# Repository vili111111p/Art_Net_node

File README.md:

# Art_Net_node
It's a node for the Art-Net protocol with 4 universes on 4 dmx outputs. It can be controlled with 3 buttons and an OLED display. Maybe i will include a web interface also.

## CAD Model
Its two parted and with a little modification can be made with a metal sheet. Now the connection is with heat inserts and screws.

## PCB
It has two layers, on both of them are components. Its controlled with an ESP32 S3, it has battery management, can be powered trough POE and USB-C.

Schematic

POE

USB-C

Charger

DMX Output

Control interface

PCB

## Firmware
I made it with ai, so it can be buggy, but as sonn as i built it together i will test it and fix them, if there are any.

## BOM
 - components (in the BOM file)
 - 3D printed parts
 - battery

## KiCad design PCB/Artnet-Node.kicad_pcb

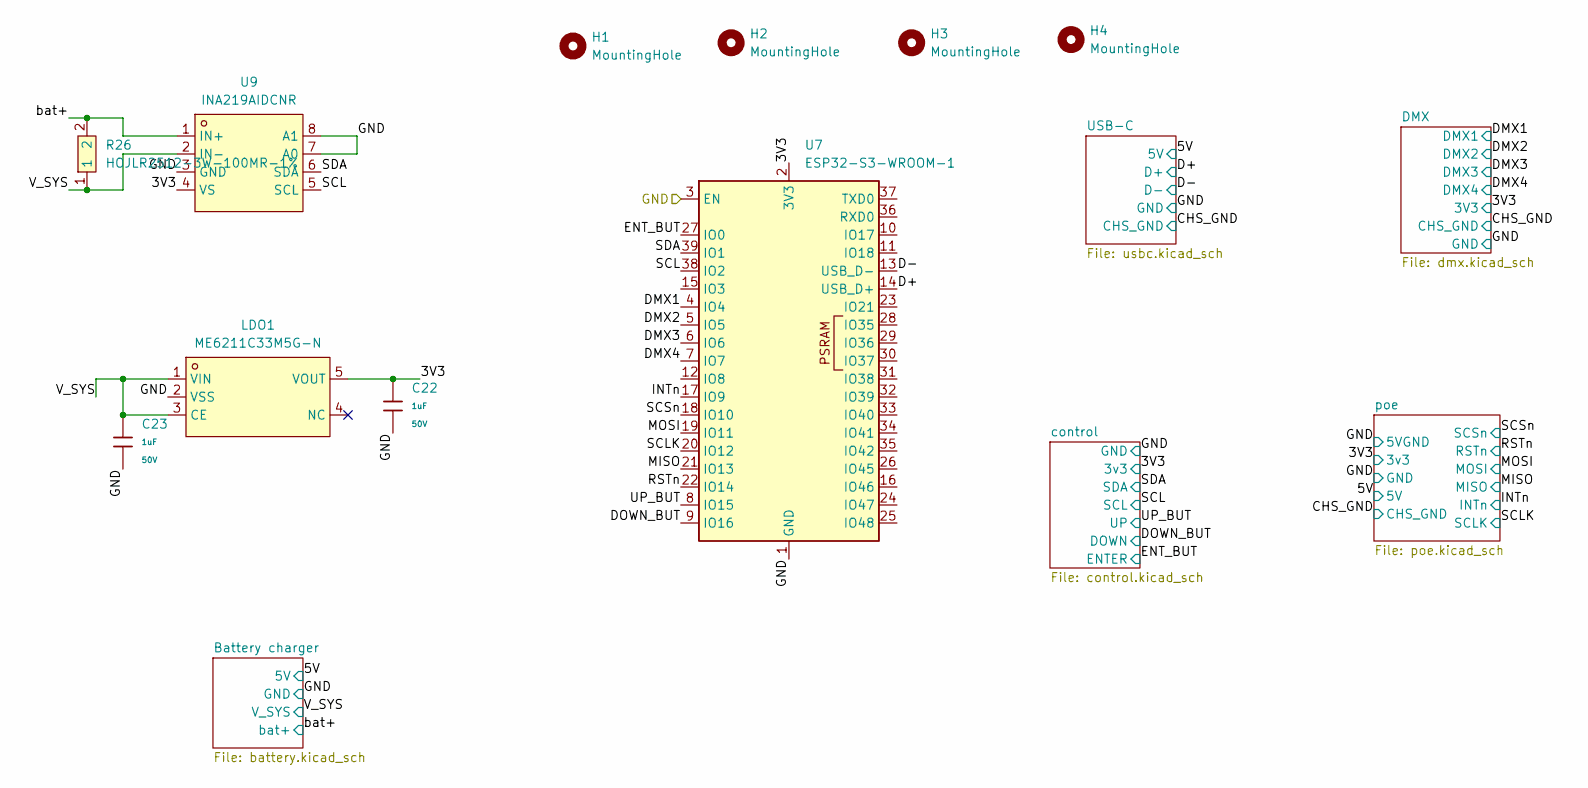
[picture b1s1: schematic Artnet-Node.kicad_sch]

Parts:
C22, C23: 1uF; C_0603; Voltage Rated 50V; Tolerance ±10%; Part CL10A105KB8NNNC; LCSC C15849
H1, H2, H3, H4: MountingHole; MountingHole_3.2mm_M3
LDO1: ME6211C33M5G-N; SOT-23-5_L3.0-W1.7-P0.95-LS2.8-BL; LCSC Part C82942
R26: HOJLR2512-3W-100MR-1%; RES-SMD_L6.4-W3.2-R2512; LCSC Part C2903476
U7: ESP32-S3-WROOM-1
U9: INA219AIDCNR; SOT-23-8_L3.0-W1.7-P0.65-LS2.8-BR; LCSC Part C87469

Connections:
+3V3D: C22.1, LDO1.5 (VOUT), U7.2 (3V3), U9.4 (VS); also elsewhere on the board
/D+: U7.14 (USB_D+); also elsewhere on the board
/D-: U7.13 (USB_D-); also elsewhere on the board
/DMX1: U7.4 (IO4); also elsewhere on the board
/DMX2: U7.5 (IO5); also elsewhere on the board
/DMX3: U7.6 (IO6); also elsewhere on the board
/DMX4: U7.7 (IO7); also elsewhere on the board
/DOWN_BUT: U7.9 (IO16); also elsewhere on the board
/ENT_BUT: U7.27 (IO0); also elsewhere on the board
/INTn: U7.17 (IO9); also elsewhere on the board
/MISO: U7.21 (IO13); also elsewhere on the board
/MOSI: U7.19 (IO11); also elsewhere on the board
/RSTn: U7.22 (IO14); also elsewhere on the board
/SCL: U7.38 (IO2), U9.5 (SCL); also elsewhere on the board
/SCLK: U7.20 (IO12); also elsewhere on the board
/SCSn: U7.18 (IO10); also elsewhere on the board
/SDA: U7.39 (IO1), U9.6 (SDA); also elsewhere on the board
/UP_BUT: U7.8 (IO15); also elsewhere on the board
/V_SYS: C23.1, LDO1.1 (VIN), LDO1.3 (CE), R26.1, U9.2 (IN-); also elsewhere on the board
/bat+: R26.2, U9.1 (IN+); also elsewhere on the board
GND: C22.2, C23.2, LDO1.2 (VSS), U7.1 (GND), U7.3 (EN), U7.40 (GND), U7.41 (GND), U9.3 (GND), U9.7 (A0), U9.8 (A1); also elsewhere on the board

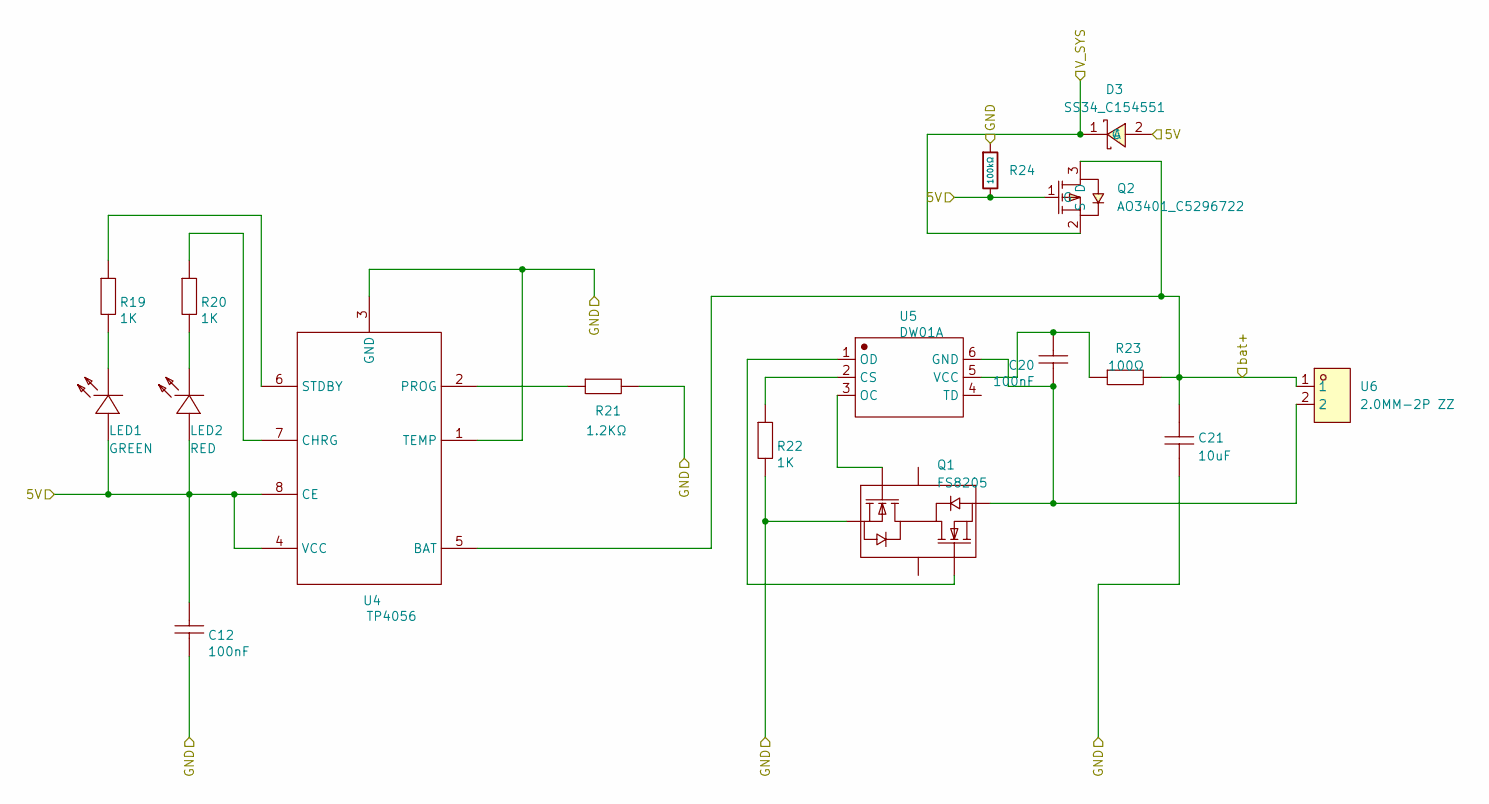
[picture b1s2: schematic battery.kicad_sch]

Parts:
C12, C20: 100nF; C_0603; MANUFACTURER PART 0603B104K250
C21: 10uF; C0603; MANUFACTURER PART CL10A106MP8NNNC
D3: SS34_C154551; SMC_L6.9-W5.9-LS7.9-RD; LCSC Part C154551
LED1: GREEN; C0603; MANUFACTURER PART LTST-C193TGKT-5A
LED2: RED; C0603; MANUFACTURER PART LTST-C191KRKT
Q1: FS8205; SOT-23-6; MANUFACTURER PART FS8205; LCSC ASSEMBLY Yes
Q2: AO3401_C5296722; SOT-23-3_L2.9-W1.3-P1.90-LS2.4-BR; LCSC Part C5296722
R19, R20, R22: 1K; R0603; MANUFACTURER PART ERJ3GEYJ102V
R21: 1.2KΩ; R0603; MANUFACTURER PART RC0603JR-071K2L
R23: 100Ω; R0603; MANUFACTURER PART 0603WAJ0101T5E
R24: 100kΩ; R_0603; Overload Voltage (Max) 75V; Tolerance ±1%; Part 0603WAF1003T5E; LCSC C25803
U4: TP4056; ESOP-8_L4.9-W3.9-P1.27-LS6.0-BL-EP; MANUFACTURER PART TP4056; LCSC ASSEMBLY Yes
U5: DW01A; SOT-23-6_L2.9-W1.6-P0.95-LS2.8-BL; MANUFACTURER PART DW01A
U6: 2.0MM-2P ZZ; CONN-TH_2P-P2.00_HX-2.0MM-2P-ZZ; LCSC Part C5368724

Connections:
/5V: C12.2, D3.2 (A), LED1.1 (A), LED2.1 (A), Q2.1 (G), R24.2, U4.4 (VCC), U4.8 (CE); also elsewhere on the board
/V_SYS: D3.1 (C), Q2.2 (S); also elsewhere on the board
/bat+: C21.2, Q2.3 (D), R23.2, U4.5 (BAT), U6.1; also elsewhere on the board
GND: C12.1, C21.1, Q1.1 (S1), R21.2, R22.1, R24.1, U4.1 (TEMP), U4.3 (GND); also elsewhere on the board
unnamed: LED1.2 (K), R19.1
unnamed: LED2.2 (K), R20.2
unnamed: Q1.6 (G1), U5.3 (OC)
unnamed: Q1.4 (G2), U5.1 (OD)
unnamed: C20.2, Q1.3 (S2), U5.6 (GND), U6.2
unnamed: R20.1, U4.7 (CHRG)
unnamed: R21.1, U4.2 (PROG)
unnamed: R19.2, U4.6 (STDBY)
unnamed: R22.2, U5.2 (CS)
unnamed: C20.1, R23.1, U5.5 (VCC)

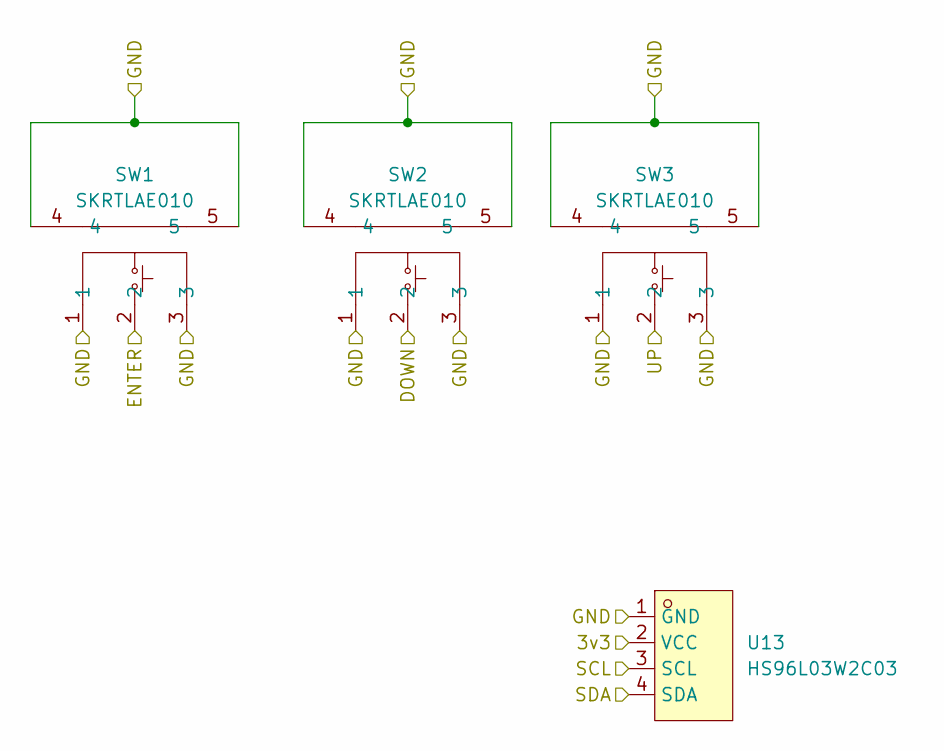
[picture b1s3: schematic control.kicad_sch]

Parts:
SW1, SW2, SW3: SKRTLAE010; KEY-SMD_SKRTLAE010; LCSC Part C110293
U13: HS96L03W2C03; OLED-TH_L27.8-W27.2-P2.54_C9900033791; LCSC Part C5248080

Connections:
+3V3D: U13.2 (VCC); also elsewhere on the board
/DOWN_BUT: SW2.2; also elsewhere on the board
/ENT_BUT: SW1.2; also elsewhere on the board
/SCL: U13.3 (SCL); also elsewhere on the board
/SDA: U13.4 (SDA); also elsewhere on the board
/UP_BUT: SW3.2; also elsewhere on the board
GND: SW1.1, SW1.3, SW1.4, SW1.5, SW2.1, SW2.3, SW2.4, SW2.5, SW3.1, SW3.3, SW3.4, SW3.5, U13.1 (GND); also elsewhere on the board

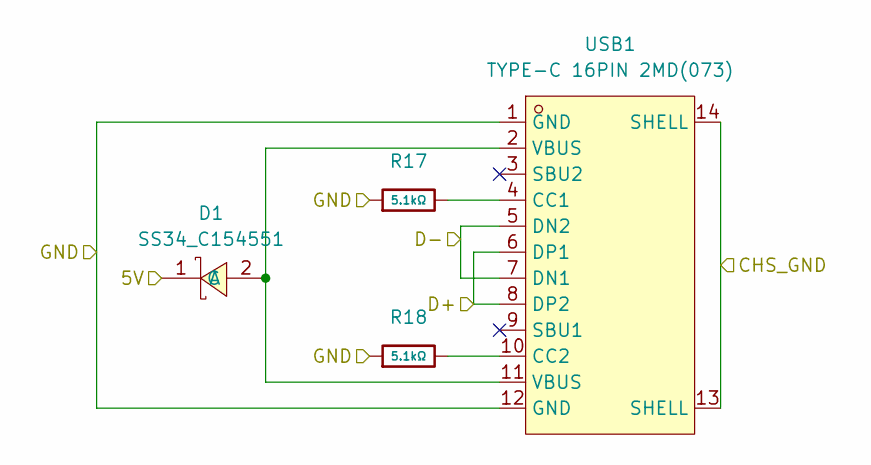
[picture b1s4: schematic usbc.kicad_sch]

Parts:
D1: SS34_C154551; SMC_L6.9-W5.9-LS7.9-RD; LCSC Part C154551
R17, R18: 5.1kΩ; R_0402; Overload Voltage (Max) 50V; Tolerance ±1%; Part 0402WGF5101TCE; LCSC C25905
USB1: TYPE-C 16PIN 2MD(073); USB-C-SMD_TYPE-C-6PIN-2MD-073; LCSC Part C2765186

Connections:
/5V: D1.1 (C); also elsewhere on the board
/CHS_GND: USB1.13 (SHELL), USB1.14 (SHELL); also elsewhere on the board
/D+: USB1.6 (DP1), USB1.8 (DP2); also elsewhere on the board
/D-: USB1.5 (DN2), USB1.7 (DN1); also elsewhere on the board
GND: R17.1, R18.1, USB1.1 (GND), USB1.12 (GND); also elsewhere on the board
unnamed: D1.2 (A), USB1.2 (VBUS), USB1.11 (VBUS)
unnamed: R17.2, USB1.4 (CC1)
unnamed: R18.2, USB1.10 (CC2)

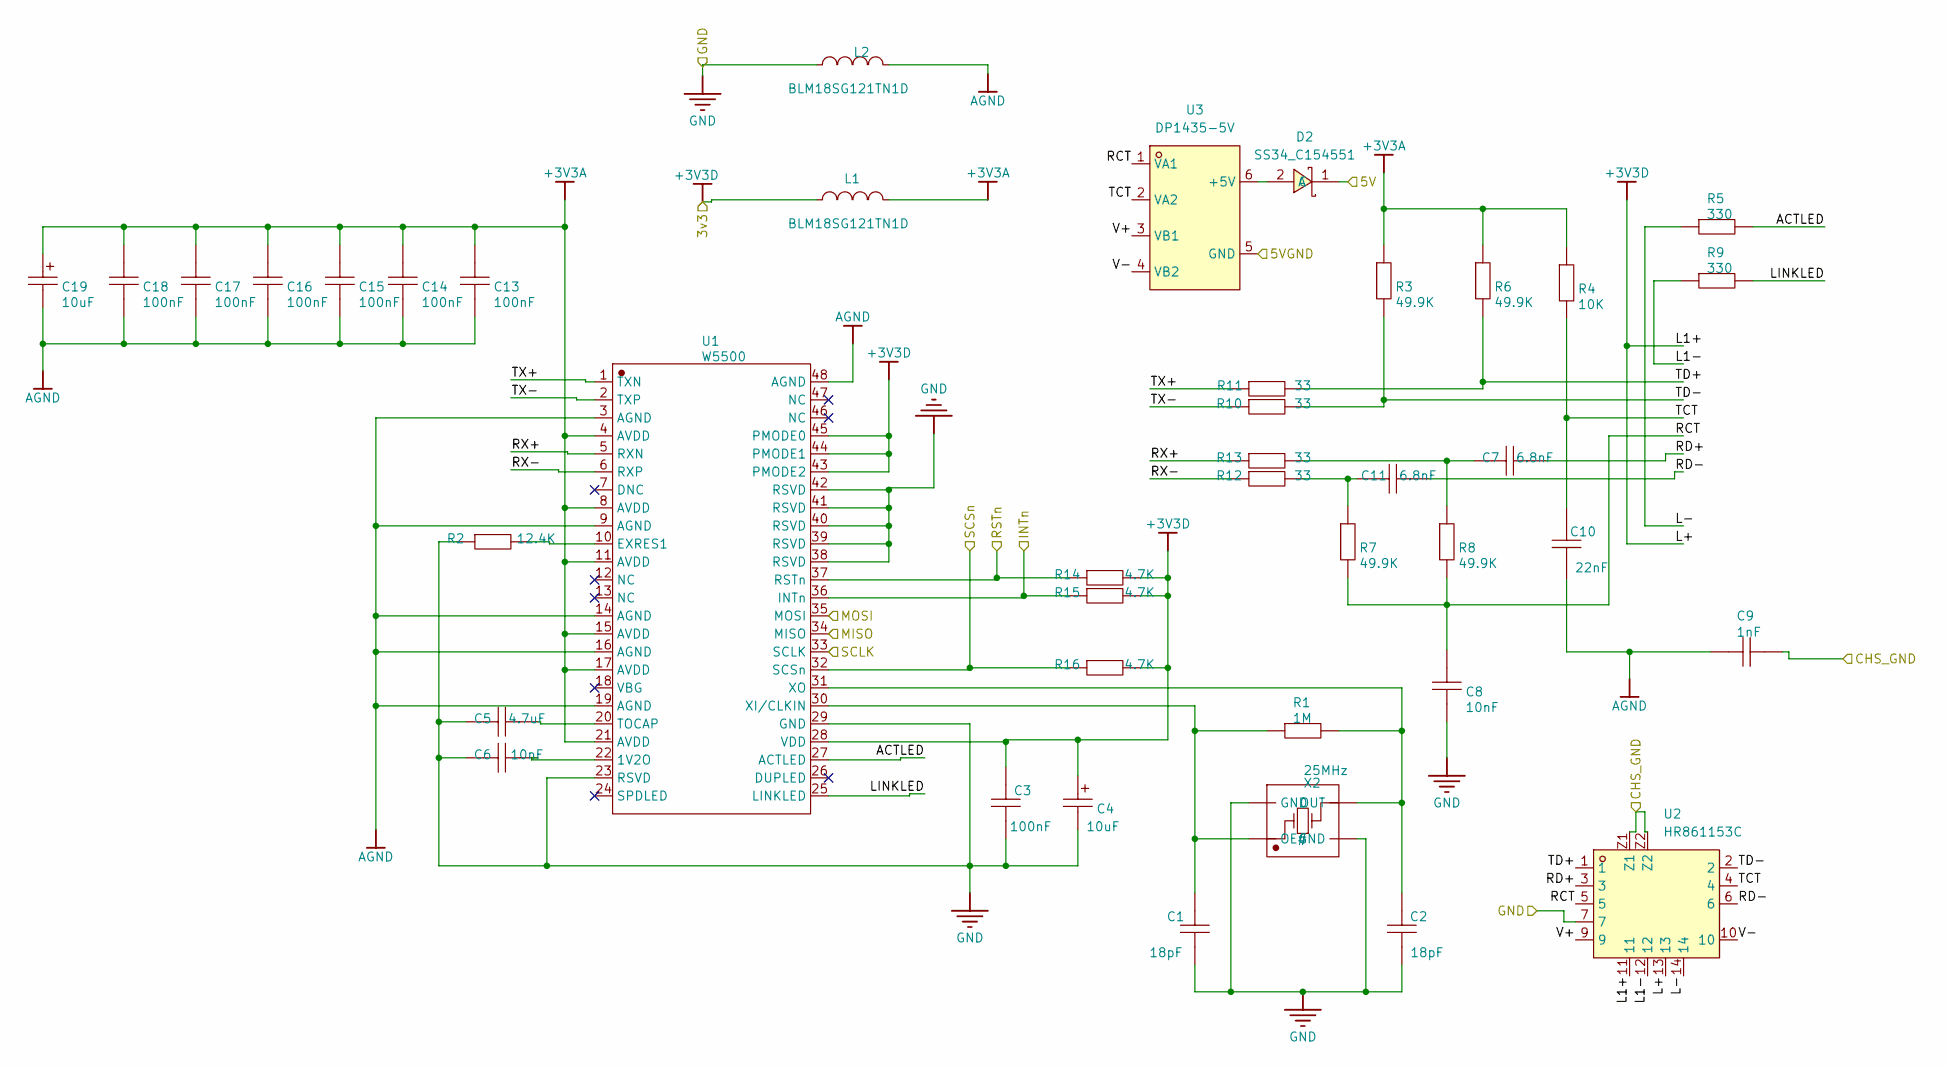
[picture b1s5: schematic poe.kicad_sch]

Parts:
C1, C2: 18pF; C_0603; MANUFACTURER PART GRM1882C1H180JA01D
C3, C13, C14, C15, C16, C17, C18: 100nF; C_0603; MANUFACTURER PART GCM188R71C104KA37D
C4, C19: 10uF; CASE-A_3216; MANUFACTURER PART T491A106K016AT; LCSC ASSEMBLY Yes
C5: 4.7uF; C0603; MANUFACTURER PART GRM188Z71C475KE21D
C6, C8: 10nF; C0603; MANUFACTURER PART GRM188R71C103KA01D
C7, C11: 6.8nF; C0603; MANUFACTURER PART GCM188R71H682KA37D
C9: 1nF; C1206; MANUFACTURER PART GR431BR7LA102KW66L
C10: 22nF; C0603; MANUFACTURER PART GCE188R71H223KA01D
D2: SS34_C154551; SMC_L6.9-W5.9-LS7.9-RD; LCSC Part C154551
L1, L2: BLM18SG121TN1D; C0603; MANUFACTURER PART BLM18SG121TN1D
R1: 1M; R0603; MANUFACTURER PART RC0603JR-071ML
R2: 12.4K; R0603; MANUFACTURER PART RC0603FR-0712K4L
R3, R6, R7, R8: 49.9K; R0603; MANUFACTURER PART RC0603FR-0749K9L
R4: 10K; R0603; MANUFACTURER PART RC0603FR-0710KL
R5, R9: 330; R0603; MANUFACTURER PART RC0603FR-07330RL
R10, R11, R12, R13: 33; R0603; MANUFACTURER PART RC0603FR-0733RL
R14, R15, R16: 4.7K; R0603; MANUFACTURER PART RC0603FR-074K7L
U1: W5500; LQFP-48_L7.0-W7.0-P0.50-LS9.0-BL; MANUFACTURER PART W5500; LCSC ASSEMBLY Yes
U2: HR861153C; RJ45-TH_ARJP11A-MASA-B-A-EMU2; LCSC Part C19724782
U3: DP1435-5V; PWRM-TH_DP1435-XX; LCSC Part C5380097
X2: 25MHz; CRYSTAL-SMD_4P-L3.2-W2.5-BL-1; MANUFACTURER PART XXGCCLNANF-25M; LCSC ASSEMBLY Yes

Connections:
+3V3A: C13.2, C14.2, C15.2, C16.2, C17.2, C18.2, C19.1, L1.2, R3.2, R4.2, R6.2, U1.4 (AVDD), U1.8 (AVDD), U1.11 (AVDD), U1.15 (AVDD), U1.17 (AVDD), U1.21 (AVDD)
+3V3D: C3.2, C4.1, L1.1, R14.2, R15.2, R16.2, U1.28 (VDD), U1.43 (PMODE2), U1.44 (PMODE1), U1.45 (PMODE0), U2.11, U2.13; also elsewhere on the board
/5V: D2.1 (C); also elsewhere on the board
/CHS_GND: C9.1, U2.Z1, U2.Z2; also elsewhere on the board
/INTn: R15.1, U1.36 (INTn); also elsewhere on the board
/MISO: U1.34 (MISO); also elsewhere on the board
/MOSI: U1.35 (MOSI); also elsewhere on the board
/RSTn: R14.1, U1.37 (RSTn); also elsewhere on the board
/SCLK: U1.33 (SCLK); also elsewhere on the board
/SCSn: R16.1, U1.32 (SCSn); also elsewhere on the board
/poe/ACTLED: R5.1, U1.27 (ACTLED)
/poe/L1-: R9.2, U2.12
/poe/L-: R5.2, U2.14
/poe/LINKLED: R9.1, U1.25 (LINKLED)
/poe/RCT: C8.2, R7.1, R8.1, U2.5, U3.1 (VA1)
/poe/RD+: C7.1, U2.3
/poe/RD-: C11.1, U2.6
/poe/RX+: R13.1, U1.5 (RXN)
/poe/RX-: R12.1, U1.6 (RXP)
/poe/TCT: C10.1, R4.1, U2.4, U3.2 (VA2)
/poe/TD+: R6.1, R11.2, U2.1
/poe/TD-: R3.1, R10.2, U2.2
/poe/TX+: R11.1, U1.1 (TXN)
/poe/TX-: R10.1, U1.2 (TXP)
/poe/V+: U2.9, U3.3 (VB1)
/poe/V-: U2.10, U3.4 (VB2)
AGND: C9.2, C10.2, C13.1, C14.1, C15.1, C16.1, C17.1, C18.1, C19.2, L2.2, U1.3 (AGND), U1.9 (AGND), U1.14 (AGND), U1.16 (AGND), U1.19 (AGND), U1.48 (AGND)
GND: C1.1, C2.1, C3.1, C4.2, C5.2, C6.2, C8.1, L2.1, R2.1, U1.23 (RSVD), U1.29 (GND), U1.38 (RSVD), U1.39 (RSVD), U1.40 (RSVD), U1.41 (RSVD), U1.42 (RSVD), U2.7, U3.5 (GND), X2.2 (GND), X2.4 (GND); also elsewhere on the board
unnamed: C7.2, R8.2, R13.2
unnamed: C11.2, R7.2, R12.2
unnamed: D2.2 (A), U3.6 (+5V)
unnamed: C6.1, U1.22 (1V2O)
unnamed: R2.2, U1.10 (EXRES1)
unnamed: C5.1, U1.20 (TOCAP)
unnamed: C1.2, R1.1, U1.30 (XI/CLKIN), X2.1 (OE#)
unnamed: C2.2, R1.2, U1.31 (XO), X2.3 (OUT)

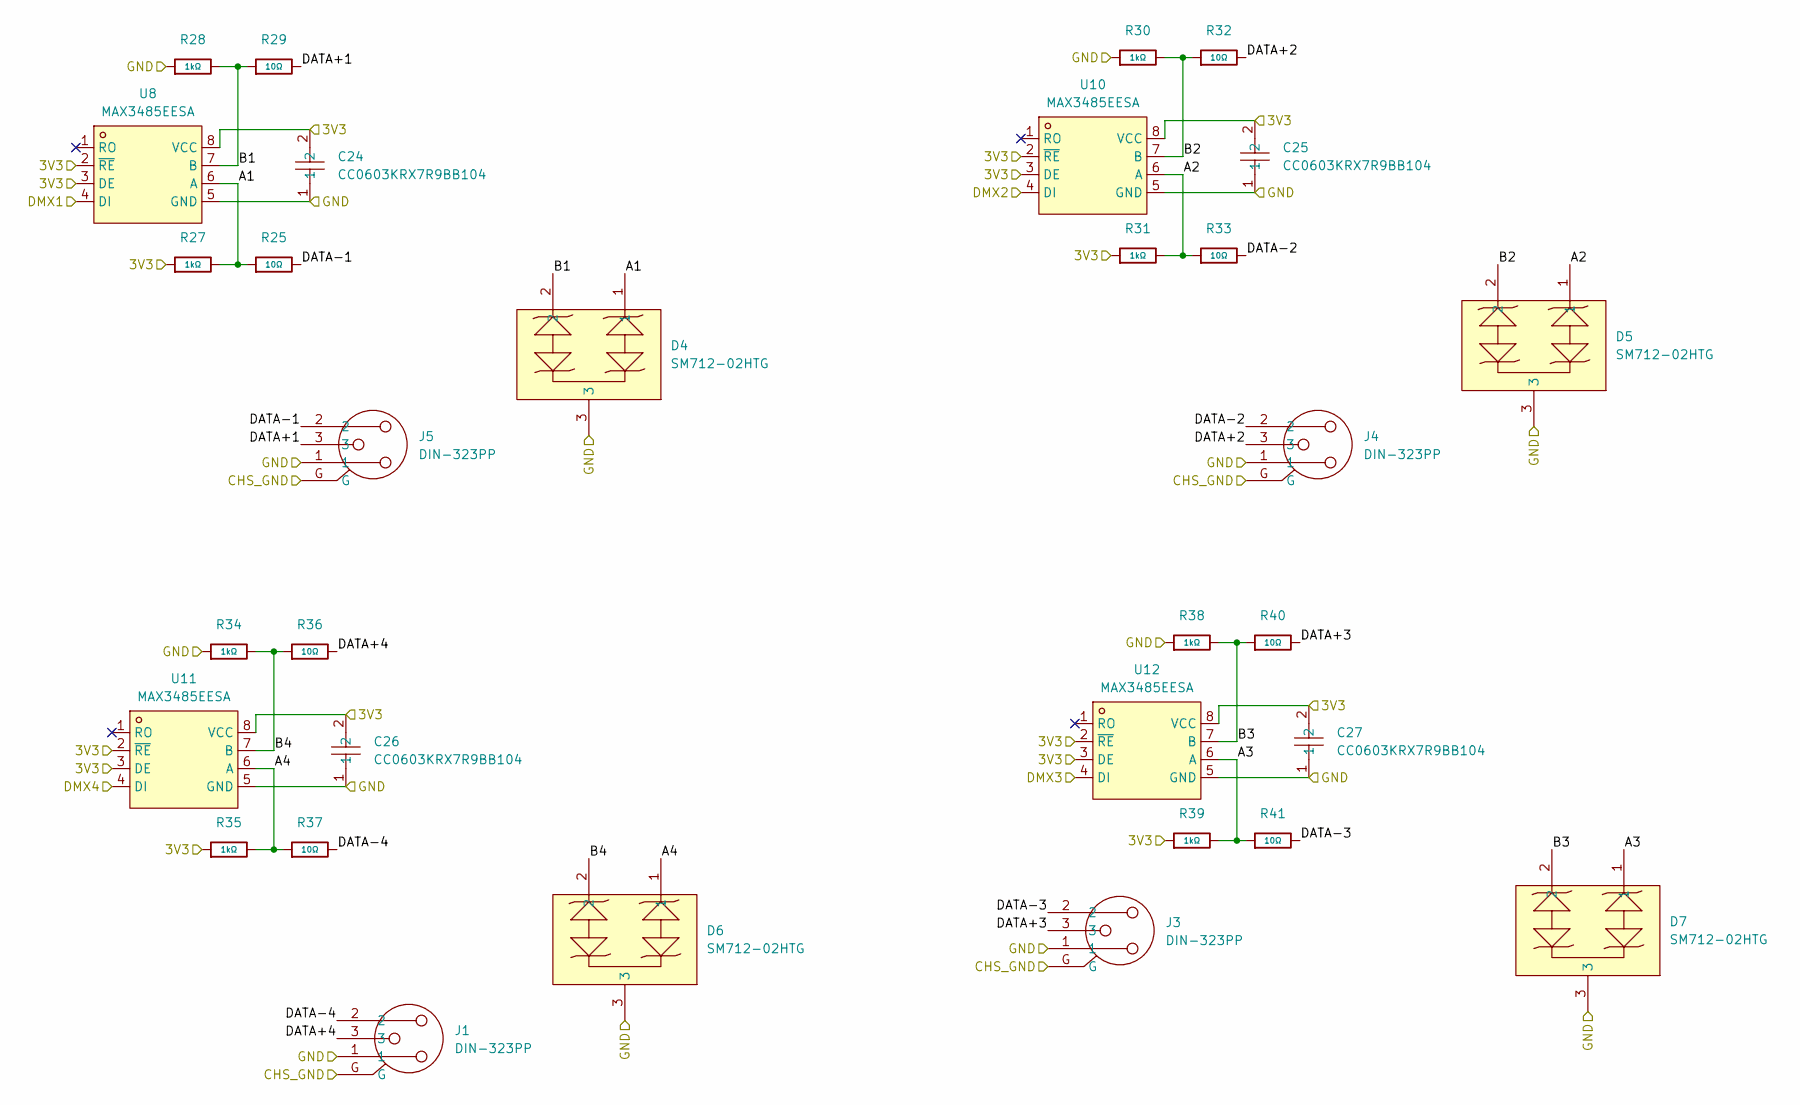
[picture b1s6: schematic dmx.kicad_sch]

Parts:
C24, C25, C26, C27: CC0603KRX7R9BB104; C0603; LCSC Part C14663
D4, D5, D6, D7: SM712-02HTG; SOT-23_L2.9-W1.3-P1.90-LS2.4-BR; LCSC Part C172881
J1, J3, J4, J5: DIN-323PP; CONN-TH_DIN-323PP; LCSC Part C309317
R25, R29, R32, R33, R36, R37, R40, R41: 10Ω; R_0603; Overload Voltage (Max) 75V; Tolerance ±1%; Part 0603WAF100JT5E; LCSC C22859
R27, R28, R30, R31, R34, R35, R38, R39: 1kΩ; R_0603; Overload Voltage (Max) 75V; Tolerance ±1%; Part 0603WAF1001T5E; LCSC C21190
U8, U10, U11, U12: MAX3485EESA; SOIC-8_L4.9-W3.9-P1.27-LS6.0-BL; LCSC Part C9943

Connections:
+3V3D: C24.2, C25.2, C26.2, C27.2, R27.1, R31.1, R35.1, R39.1, U8.2 (~RE), U8.3 (DE), U8.8 (VCC), U10.2 (~RE), U10.3 (DE), U10.8 (VCC), U11.2 (~RE), U11.3 (DE), U11.8 (VCC), U12.2 (~RE), U12.3 (DE), U12.8 (VCC); also elsewhere on the board
/CHS_GND: J1.G, J3.G, J4.G, J5.G; also elsewhere on the board
/DMX1: U8.4 (DI); also elsewhere on the board
/DMX2: U10.4 (DI); also elsewhere on the board
/DMX3: U12.4 (DI); also elsewhere on the board
/DMX4: U11.4 (DI); also elsewhere on the board
/DMX/A1: D4.1, R25.1, R27.2, U8.6 (A)
/DMX/A2: D5.1, R31.2, R33.1, U10.6 (A)
/DMX/A3: D7.1, R39.2, R41.1, U12.6 (A)
/DMX/A4: D6.1, R35.2, R37.1, U11.6 (A)
/DMX/B1: D4.2, R28.2, R29.1, U8.7 (B)
/DMX/B2: D5.2, R30.2, R32.1, U10.7 (B)
/DMX/B3: D7.2, R38.2, R40.1, U12.7 (B)
/DMX/B4: D6.2, R34.2, R36.1, U11.7 (B)
/DMX/DATA+1: J5.3, R29.2
/DMX/DATA+2: J4.3, R32.2
/DMX/DATA+3: J3.3, R40.2
/DMX/DATA+4: J1.3, R36.2
/DMX/DATA-1: J5.2, R25.2
/DMX/DATA-2: J4.2, R33.2
/DMX/DATA-3: J3.2, R41.2
/DMX/DATA-4: J1.2, R37.2
GND: C24.1, C25.1, C26.1, C27.1, D4.3, D5.3, D6.3, D7.3, J1.1, J3.1, J4.1, J5.1, R28.1, R30.1, R34.1, R38.1, U8.5 (GND), U10.5 (GND), U11.5 (GND), U12.5 (GND); also elsewhere on the board

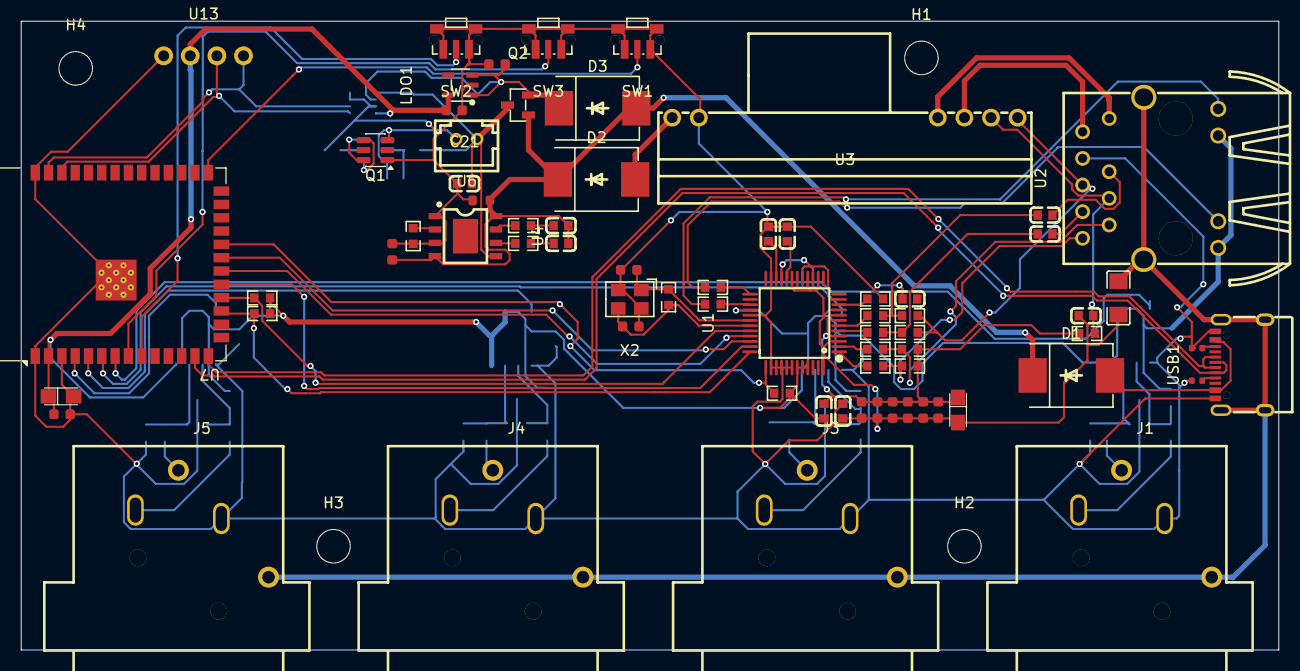
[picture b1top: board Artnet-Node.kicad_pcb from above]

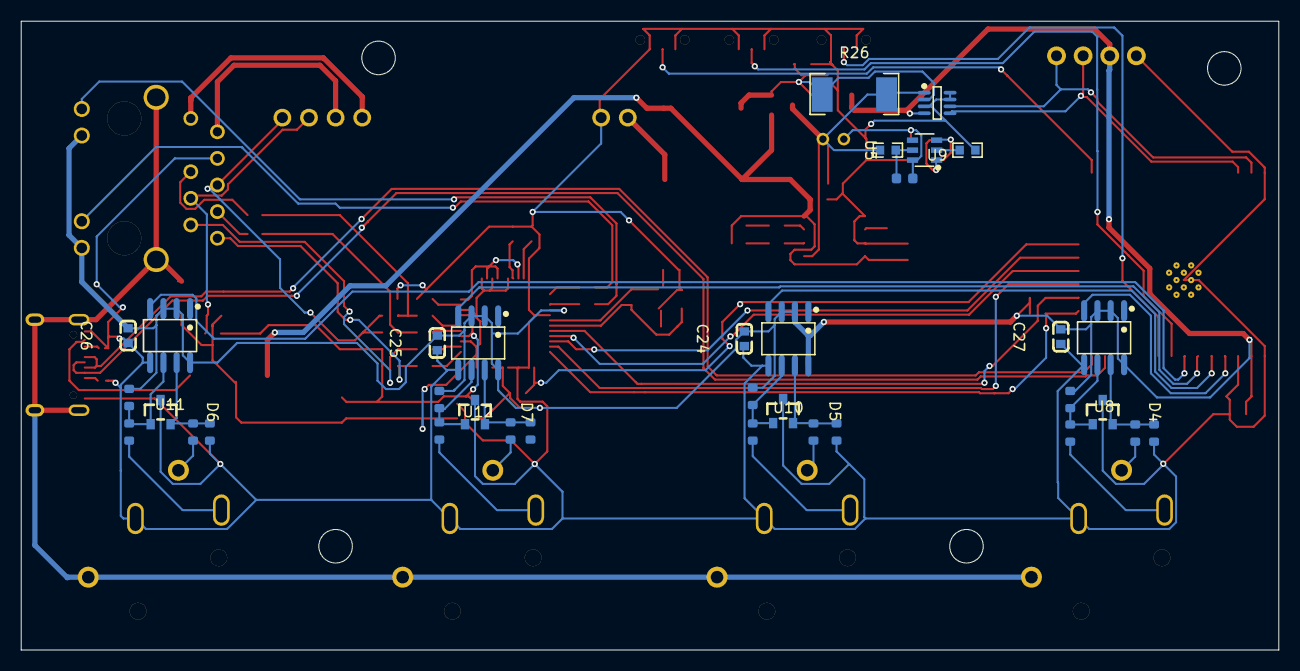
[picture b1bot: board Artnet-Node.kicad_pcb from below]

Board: 2 copper layers, 120.0 x 60.0 mm, 108 parts (34 on the bottom side), 78 nets.

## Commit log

2026-01-03 Enhance README with additional project details
    Expanded the README to include details about the CAD model, PCB, firmware, and BOM.
2026-01-03 uploading files
2026-01-03 File uploading
2026-02-10 Add images for POE, USB-C, Charger, and DMX Output
